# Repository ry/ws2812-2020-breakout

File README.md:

# kicad breakout pcb for ws2812-2020 LEDs

Datasheet: http://www.peace-corp.co.jp/data/WS2812-2020_V1.0_EN.pdf

Buy: https://www.aliexpress.com/item/32888947042.html?spm=a2g0s.9042311.0.0.7f244c4dAb2u6V

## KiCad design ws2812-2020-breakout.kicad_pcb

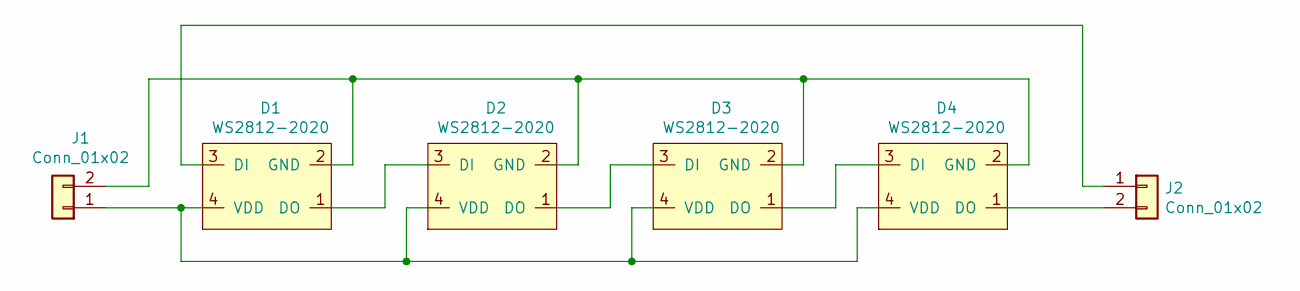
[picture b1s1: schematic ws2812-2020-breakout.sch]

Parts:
D1, D2, D3, D4: WS2812-2020; WS2812-2020-2.00mmx2.20mm
J1, J2: Conn_01x02; PinSocket_1x02_P2.54mm_Vertical

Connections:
unnamed: D1.1 (DO), D2.3 (DI)
unnamed: D1.2 (GND), D2.2 (GND), D3.2 (GND), D4.2 (GND), J1.2
unnamed: D1.3 (DI), J2.1
unnamed: D1.4 (VDD), D2.4 (VDD), D3.4 (VDD), D4.4 (VDD), J1.1
unnamed: D2.1 (DO), D3.3 (DI)
unnamed: D3.1 (DO), D4.3 (DI)
unnamed: D4.1 (DO), J2.2

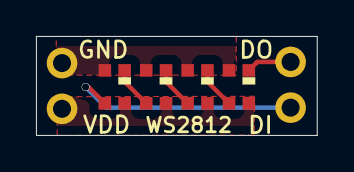
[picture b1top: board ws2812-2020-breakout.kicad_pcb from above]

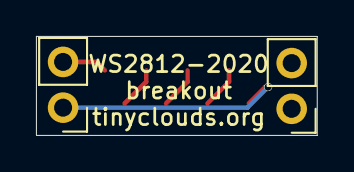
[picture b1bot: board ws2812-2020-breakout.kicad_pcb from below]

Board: 2 copper layers, 15.6 x 5.5 mm, 6 parts (2 on the bottom side), 7 nets.

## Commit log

2019-11-15 init
2019-11-15 add outputs
2019-11-15 add readme
2019-11-15 improve schematics
2019-11-21 add image of soldered board
